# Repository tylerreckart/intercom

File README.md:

# Intercom

A custom, local-first **voice bridge** for [Arbiter](https://arbiter.run): ESP32 (or any client) speaks PCM in, Intercom runs **whisper.cpp** STT + **Kokoro** TTS, and Arbiter stays text + SSE in the middle.

```
ESP32  --WS PCM while PTT held-->  Intercom  --text/SSE-->  arbiter --api
ESP32  <--WS reply PCM-----------  Intercom  <--text------/
```

HTTP `POST /v1/utterance` on `:8090` remains the fallback if the WebSocket is down.

Intercom keeps Whisper and Kokoro loaded in local HTTP servers (`whisper-server` on `:8092`, `scripts/kokoro_server.py` on `:8091`) so each turn does not reload ONNX/ggml. Instant-ack phrases (`Yes, sir.`, `Of course.`, `Very good.`, …) are synthesized once at startup and replayed from PCM cache — including a local ack after `filler.instant_ack_ms` and an earlier tool ack after `filler.tool_ack_ms`. Spoken replies can start after about seven words (`early_flush_words`), not only at a period. Optional WebSocket duplex is `ws://<host>:8093/v1/stream`. Each turn logs a single `intercom latency …` line (`stt_ms`, `arbiter_ttft_ms`, `kokoro_ms`, `ttfa_ms`).

Colocate Intercom on the same host as `arbiter --api` (default `http://127.0.0.1:8080`). Device tokens never see the Arbiter bearer.

The default agent is **Arthur** — a British voice assistant with full Arbiter tool access (`config/arthur.agent.json`). Hallway commands (timers, lights, volume, home weather, next alarm) skip Arbiter when `home.ha_base_url` and `home.ha_token` point at Home Assistant. At boot Intercom sends a silent `PREFIX WARM` turn so a local model can cache Arthur's constitution before the first PTT.

## Build

```bash
cmake -S . -B build -DCMAKE_BUILD_TYPE=Release
cmake --build build -j
```

Requires C++20, CMake 3.20+, SQLite3, Threads. Fetches cpp-httplib and nlohmann/json.

## Configure

```bash
cp config/intercom.example.json intercom.json
# set arbiter_token, paths to whisper-cli + model, kokoro binary + voice
./build/intercom --config intercom.json
```

Install speech tools separately (not vendored):

- [whisper.cpp](https://github.com/ggerganov/whisper.cpp) → `whisper-cli` + `whisper-server` + `ggml-base.en.bin`
- [Kokoro](https://github.com/hexgrad/kokoro) → `kokoro-tts` + ONNX model and voices bundle (Intercom starts `scripts/kokoro_server.py` with that venv)

Set `whisper.use_server` / `kokoro.use_server` to `false` to force the old one-shot CLI path. Point `server_url` at an already-running daemon to skip spawn.

## Quick test (no mic)

Fast-path (skips Arbiter):

```bash
curl -N -H "Authorization: Bearer dev-device-secret-change-me" \
  -H "X-Device-Id: speaker-1" \
  -H "Content-Type: application/json" \
  -d '{"text":"what time is it"}' \
  --output reply.pcm \
  http://127.0.0.1:8090/v1/utterance/text
```

Play: `ffplay -f s16le -ar 16000 -ac 1 reply.pcm`

PCM utterance: see [docs/api.md](docs/api.md) and [docs/device.md](docs/device.md).

## License

Apache-2.0

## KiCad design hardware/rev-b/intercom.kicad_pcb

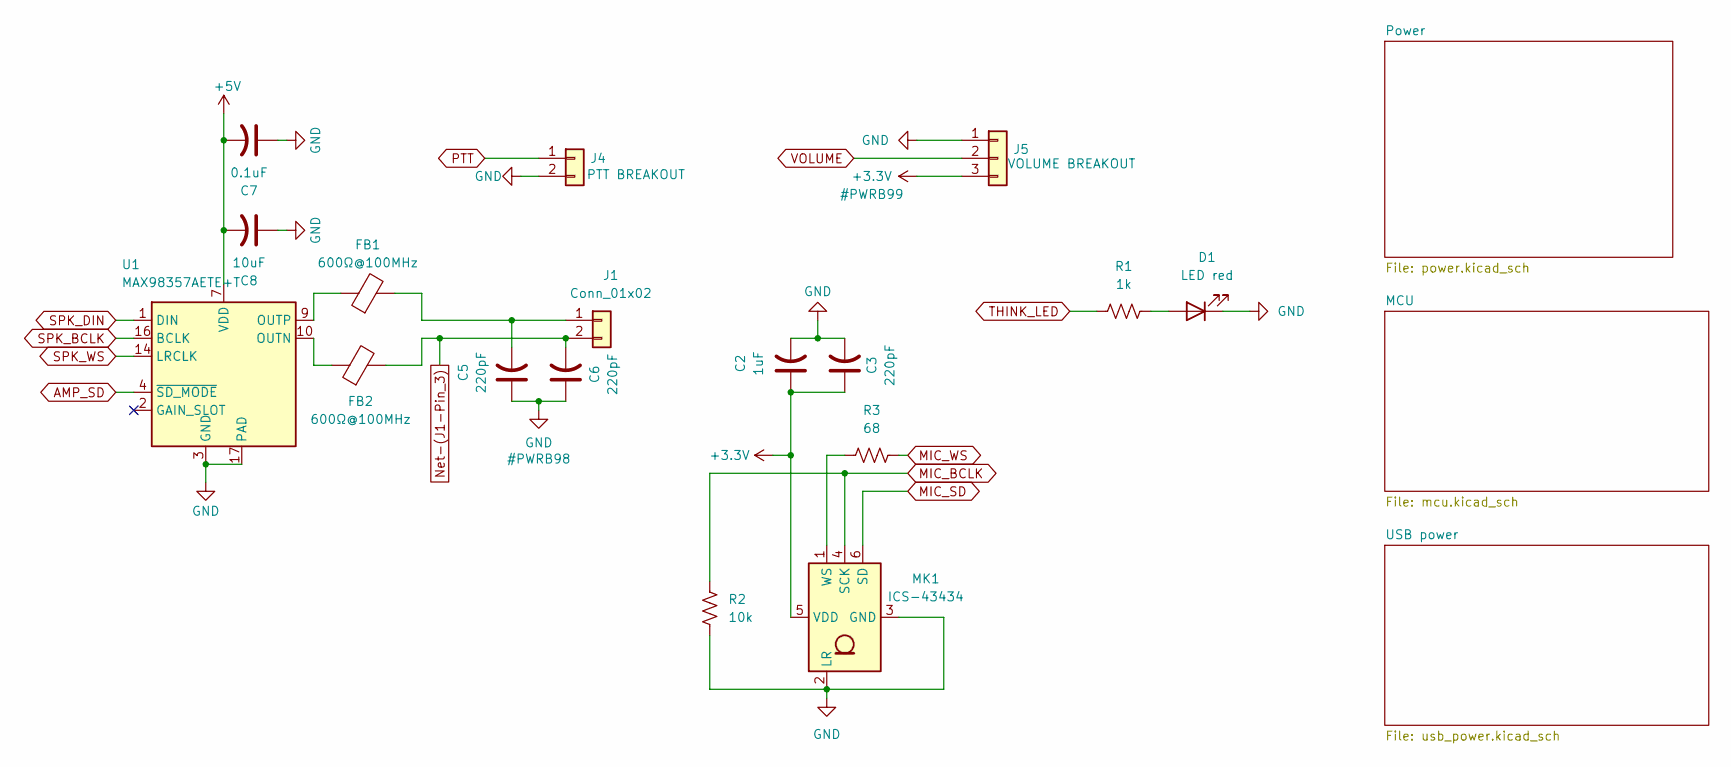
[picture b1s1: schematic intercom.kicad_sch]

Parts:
C2: 1uF; C_0402_1005Metric; MPN CL05A105KO5NNNC; LCSC C29266
C3, C5, C6: 220pF; C_0201_0603Metric; MPN CL03B221KA3NNNC; LCSC C3887425
C7: 0.1uF; C_0201_0603Metric; MPN CL03A104KP3NN5C; LCSC C307382
C8: 10uF; C_0603_1608Metric; MPN CL10A106MO8NQNC; LCSC C92487
D1: LED red; LED_0402_1005Metric; MPN HS-0402-UR; LCSC C1322304
FB1, FB2: 600Ω@100MHz; L_0805_2012Metric_Pad1.05x1.20mm_HandSolder; MPN MPZ2012S601AT000; LCSC C21519
J1: Conn_01x02; JST_PH_S2B-PH-SM4-TB_1x02-1MP_P2.00mm_Horizontal; MPN S2B-PH-SM4-TB(LF)(SN); LCSC C295747
J4: PTT BREAKOUT; JST_PH_S2B-PH-SM4-TB_1x02-1MP_P2.00mm_Horizontal; MPN S2B-PH-SM4-TB(LF)(SN); LCSC C295747
J5: VOLUME BREAKOUT; JST_PH_S3B-PH-SM4-TB_1x03-1MP_P2.00mm_Horizontal; MPN S3B-PH-SM4-TB; LCSC C20089272
MK1: ICS-43434; InvenSense_ICS-43434-6_3.5x2.65mm; MPN ICS-43434; LCSC C5656610
R1: 1k; R_0201_0603Metric; MPN 0201WMF1001TEE; LCSC C270365
R2: 10k; R_0201_0603Metric; MPN 0201WMF1002TEE; LCSC C473048
R3: 68; R_0201_0603Metric; MPN 0201WMF680JTEE; LCSC C473537
U1: MAX98357AETE+T; TQFN-16-1EP_3x3mm_P0.5mm_EP1.23x1.23mm_ThermalVias; MPN MAX98357AETE+T; LCSC C910544

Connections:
+3.3V: C2.1, C3.1, J5.3, MK1.5 (VDD); also elsewhere on the board
+5V: C7.2, C8.2, U1.7 (VDD), U1.8 (VDD); also elsewhere on the board
AMP_SD: U1.4 (~SD_MODE); also elsewhere on the board
GND: C2.2, C3.2, C5.1, C6.1, C7.1, C8.1, D1.1 (K), J4.2, J5.1, MK1.2 (LR), MK1.3 (GND), R2.1, U1.3 (GND), U1.11 (GND), U1.15 (GND), U1.17 (PAD); also elsewhere on the board
MIC_BCLK: MK1.4 (SCK), R2.2; also elsewhere on the board
MIC_SD: MK1.6 (SD); also elsewhere on the board
MIC_WS: R3.1; also elsewhere on the board
unnamed: D1.2 (A), R1.2
unnamed: C5.2, FB1.2, J1.1
unnamed: C6.2, FB2.2, J1.2
unnamed: MK1.1 (WS), R3.2
unnamed: FB2.1, U1.10 (OUTN)
unnamed: FB1.1, U1.9 (OUTP)
PTT: J4.1; also elsewhere on the board
SPK_BCLK: U1.16 (BCLK); also elsewhere on the board
SPK_DIN: U1.1 (DIN); also elsewhere on the board
SPK_WS: U1.14 (LRCLK); also elsewhere on the board
THINK_LED: R1.1; also elsewhere on the board
VOLUME: J5.2; also elsewhere on the board

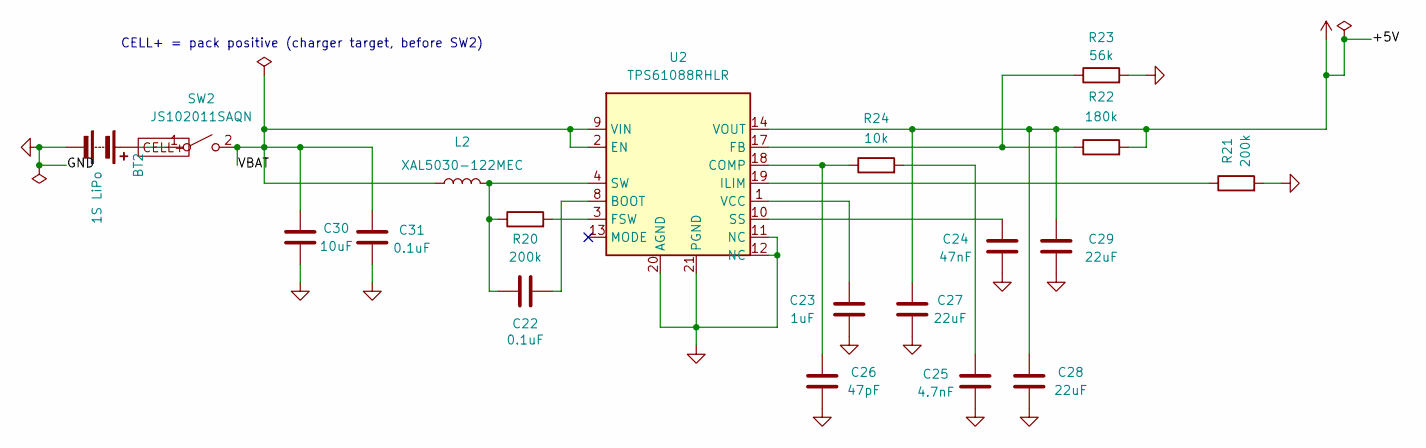
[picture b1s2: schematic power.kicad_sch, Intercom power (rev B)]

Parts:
BT2: 1S LiPo; JST_PH_S2B-PH-SM4-TB_1x02-1MP_P2.00mm_Horizontal; MPN S2B-PH-SM4-TB(LF)(SN); LCSC C295747
C22, C31: 0.1uF; C_0201_0603Metric; MPN CL03A104KP3NN5C; LCSC C307382
C23: 1uF; C_0402_1005Metric; MPN CL05A105KO5NNNC; LCSC C29266
C24: 47nF; C_0201_0603Metric; MPN 0201X473K100NT; LCSC C880416
C25: 4.7nF; C_0201_0603Metric; MPN 0201B472K100NT; LCSC C285054
C26: 47pF; C_0201_0603Metric; MPN 0201CG470J500NT; LCSC C62546
C27, C28, C29: 22uF; C_0805_2012Metric; MPN CL21A226MAQNNNE; LCSC C45783
C30: 10uF; C_0603_1608Metric; MPN CL10A106MO8NQNC; LCSC C92487
L2: XAL5030-122MEC; L_Coilcraft_XAL5030-XXX; MPN XAL5030-122MEC; LCSC C7471471
R20, R21: 200k; R_0201_0603Metric; MPN 0201WMF2003TCE; LCSC C62188
R22: 180k; R_0201_0603Metric; MPN 0201WMF1803TEE; LCSC C473559
R23: 56k; R_0201_0603Metric; MPN 0201WMF5602TEE; LCSC C473524
R24: 10k; R_0201_0603Metric; MPN 0201WMF1002TEE; LCSC C473048
SW2: JS102011SAQN; SW_SPDT_CK_JS102011SAQN; MPN JS102011SAQN; LCSC C221660
U2: TPS61088RHLR; Texas_VQFN-RHL-20_ThermalVias; MPN TPS61088RHLR; LCSC C87357

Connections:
+5V: C27.1, C28.1, C29.1, R22.2, U2.14 (VOUT), U2.15 (VOUT), U2.16 (VOUT); also elsewhere on the board
/Power/VBAT: C30.1, C31.1, L2.1, SW2.2 (B), U2.2 (EN), U2.9 (VIN)
CELL+: BT2.1 (+), SW2.1 (A); also elsewhere on the board
GND: BT2.2 (-), C23.2, C24.2, C25.2, C26.2, C27.2, C28.2, C29.2, C30.2, C31.2, R21.2, R23.2, U2.11 (NC), U2.12 (NC), U2.20 (AGND), U2.21 (PGND); also elsewhere on the board
unnamed: C22.2, L2.2, R20.1, U2.4 (SW), U2.5 (SW), U2.6 (SW), U2.7 (SW)
unnamed: C25.1, R24.2
unnamed: C22.1, U2.8 (BOOT)
unnamed: C26.1, R24.1, U2.18 (COMP)
unnamed: R22.1, R23.1, U2.17 (FB)
unnamed: R20.2, U2.3 (FSW)
unnamed: R21.1, U2.19 (ILIM)
unnamed: C24.1, U2.10 (SS)
unnamed: C23.1, U2.1 (VCC)

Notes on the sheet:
CELL+ = pack positive (charger target, before SW2)

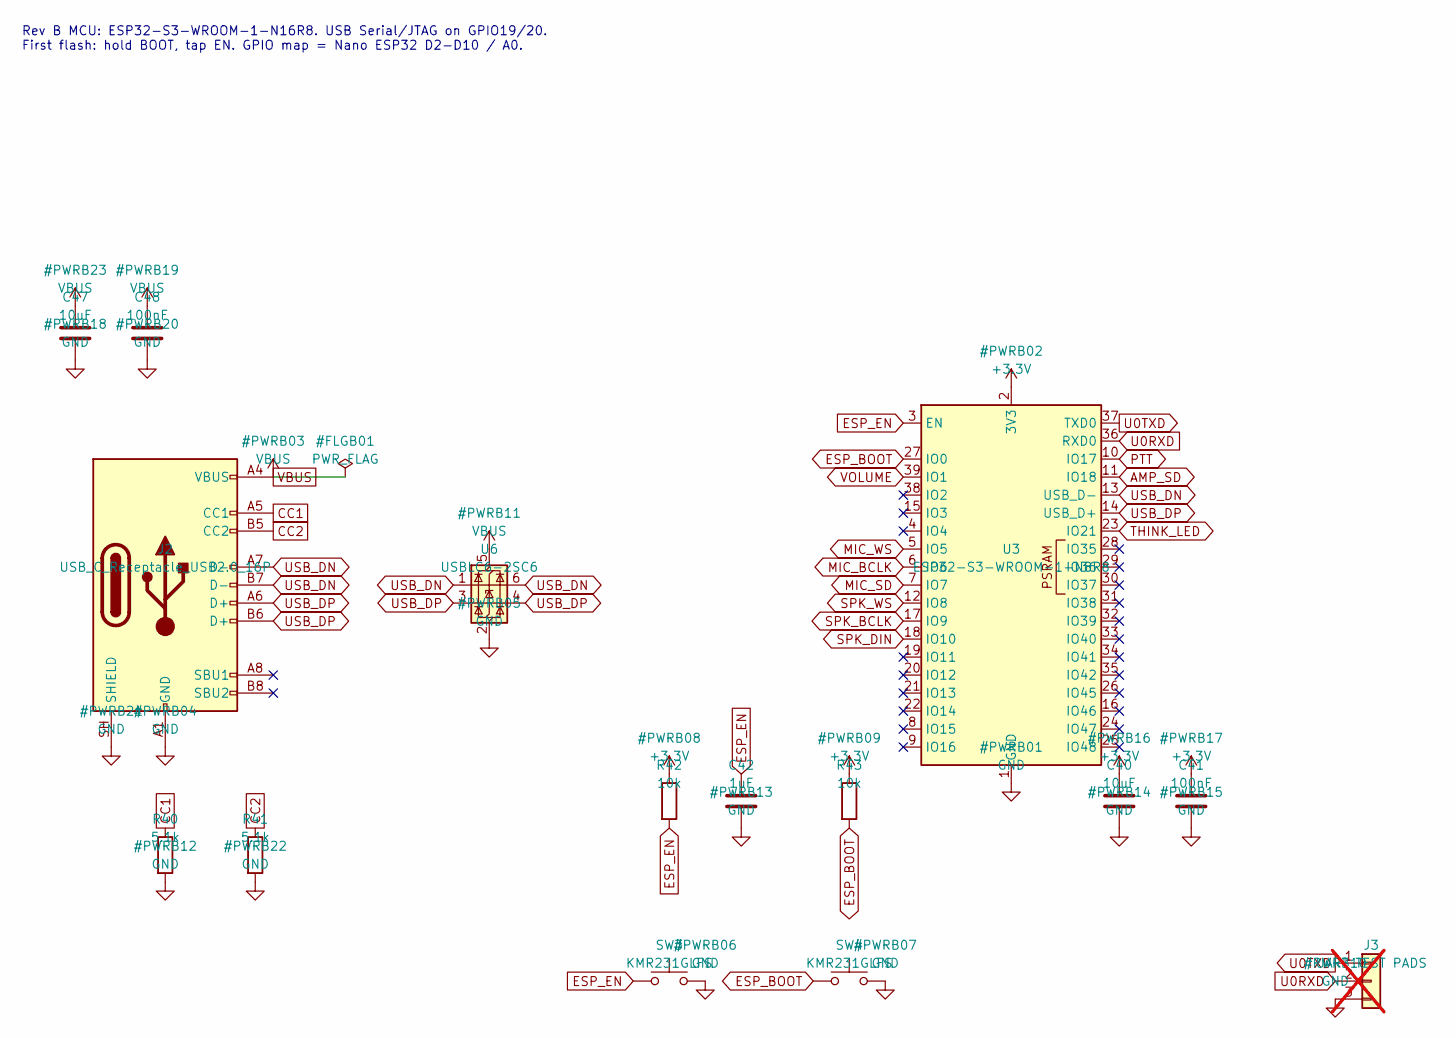
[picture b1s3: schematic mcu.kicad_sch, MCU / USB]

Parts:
C40, C47: 10uF; C_0603_1608Metric; MPN CL10A106MO8NQNC; LCSC C92487
C41, C48: 100nF; C_0201_0603Metric; MPN CL03A104KP3NN5C; LCSC C307382
C42: 1uF; C_0402_1005Metric; MPN CL05A105KO5NNNC; LCSC C29266
J2: USB_C_Receptacle_USB2.0_16P; USB_C_Receptacle_HRO_TYPE-C-31-M-12; MPN TYPE-C-31-M-12; LCSC C165948
J3: UART TEST PADS; UART_TestPads_3Pin; not fitted
R40, R41: 5.1k; R_0201_0603Metric; MPN 0201WMF5101TEE; LCSC C270344
R42, R43: 10k; R_0201_0603Metric; MPN 0201WMF1002TEE; LCSC C473048
SW3, SW4: KMR231GLFS; SW_Push_1P1T_NO_CK_KMR2; MPN KMR231GLFS; LCSC C99271
U3: ESP32-S3-WROOM-1-N8R8; ESP32-S3-WROOM-1; MPN ESP32-S3-WROOM-1-N8R8; LCSC C2913201
U6: USBLC6-2SC6; SOT-23-6; MPN USBLC6-2SC6; LCSC C7519

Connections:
+3.3V: C40.1, C41.1, R42.1, R43.1, U3.2 (3V3); also elsewhere on the board
AMP_SD: U3.11 (IO18); also elsewhere on the board
CC1: J2.A5 (CC1), R40.1
CC2: J2.B5 (CC2), R41.1
ESP_BOOT: R43.2, SW4.1, U3.27 (IO0)
ESP_EN: C42.1, R42.2, SW3.1, U3.3 (EN)
GND: C40.2, C41.2, C42.2, C47.2, C48.2, J2.A1 (GND), J2.A12 (GND), J2.B1 (GND), J2.B12 (GND), J2.SH (SHIELD), J3.3, R40.2, R41.2, SW3.2, SW4.2, U3.1 (GND), U3.40 (GND), U3.41 (GND), U6.2 (GND); also elsewhere on the board
MIC_BCLK: U3.6 (IO6); also elsewhere on the board
MIC_SD: U3.7 (IO7); also elsewhere on the board
MIC_WS: U3.5 (IO5); also elsewhere on the board
PTT: U3.10 (IO17); also elsewhere on the board
SPK_BCLK: U3.17 (IO9); also elsewhere on the board
SPK_DIN: U3.18 (IO10); also elsewhere on the board
SPK_WS: U3.12 (IO8); also elsewhere on the board
THINK_LED: U3.23 (IO21); also elsewhere on the board
U0RXD: J3.2, U3.36 (RXD0)
U0TXD: J3.1, U3.37 (TXD0)
USB_DN: J2.A7 (D-), J2.B7 (D-), U3.13 (USB_D-), U6.1 (I/O1), U6.6 (I/O1)
USB_DP: J2.A6 (D+), J2.B6 (D+), U3.14 (USB_D+), U6.3 (I/O2), U6.4 (I/O2)
VBUS: C47.1, C48.1, J2.A4 (VBUS), J2.A9 (VBUS), J2.B4 (VBUS), J2.B9 (VBUS), U6.5 (VBUS); also elsewhere on the board
VOLUME: U3.39 (IO1); also elsewhere on the board

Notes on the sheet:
Rev B MCU: ESP32-S3-WROOM-1-N16R8. USB Serial/JTAG on GPIO19/20. First flash: hold BOOT, tap EN. GPIO map = Nano ESP32 D2-D10 / A0.

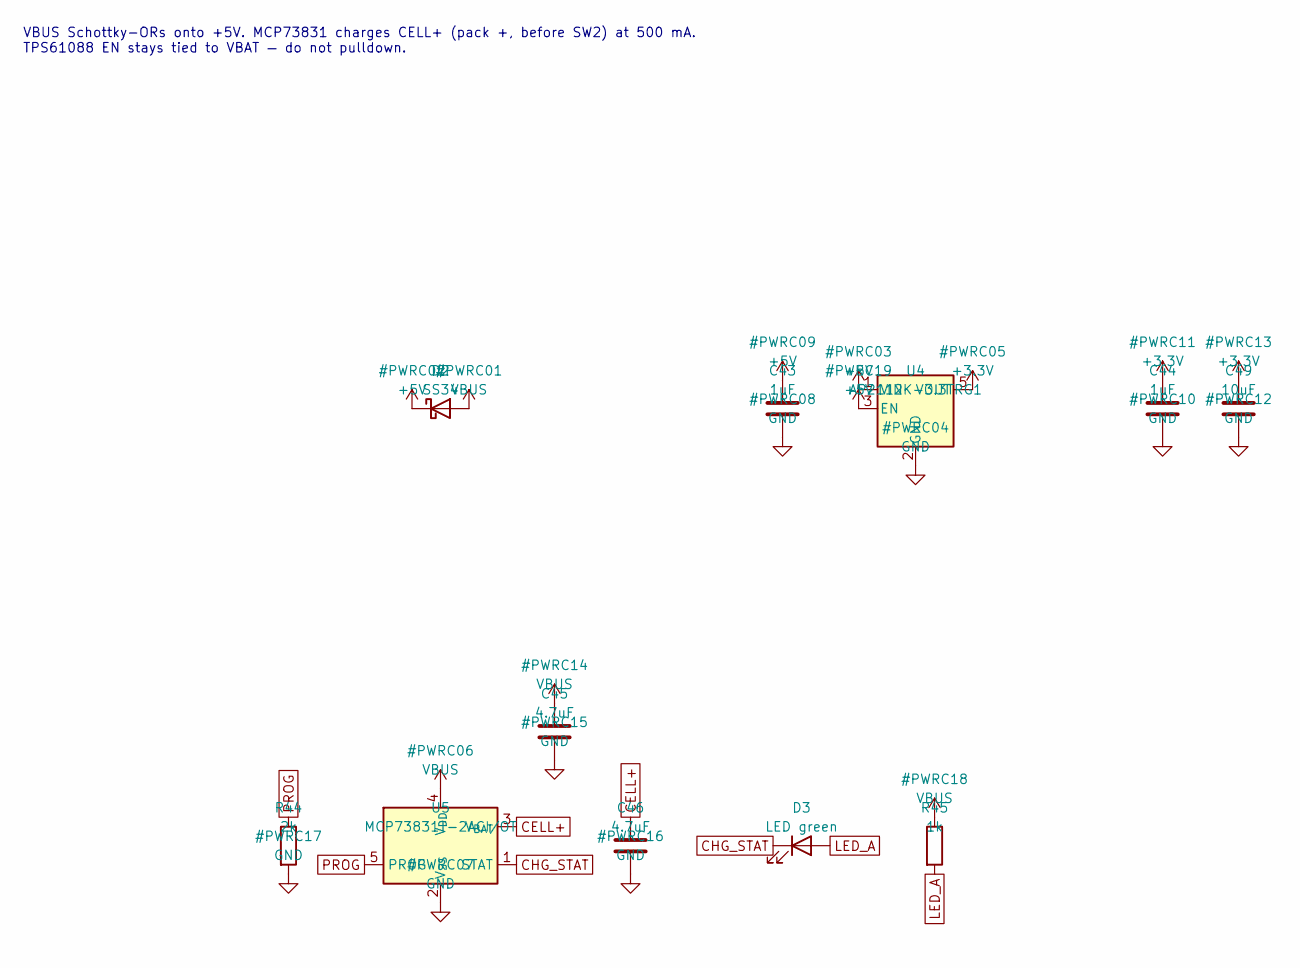
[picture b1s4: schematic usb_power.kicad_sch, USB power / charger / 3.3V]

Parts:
C43, C44: 1uF; C_0402_1005Metric; MPN CL05A105KO5NNNC; LCSC C29266
C45, C46: 4.7uF; C_0402_1005Metric; MPN CL05A475MP5NRNC; LCSC C23733
C49: 10uF; C_0603_1608Metric; MPN CL10A106MO8NQNC; LCSC C92487
D2: SS34; D_SMA; MPN SS34; LCSC C727060
D3: LED green; LED_0402_1005Metric; MPN HS-0402-UG; LCSC C1322308
R44: 2k; R_0201_0603Metric; MPN 0201WMF2001TEE; LCSC C270358
R45: 1k; R_0201_0603Metric; MPN 0201WMF1001TEE; LCSC C270365
U4: AP2112K-3.3TRG1; SOT-23-5; MPN AP2112K-3.3TRG1; LCSC C51118
U5: MCP73831T-2ACI/OT; SOT-23-5; MPN MCP73831T-2ACI/OT; LCSC C424093

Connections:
+3.3V: C44.1, C49.1, U4.5 (VOUT); also elsewhere on the board
+5V: C43.1, D2.1 (K), U4.1 (VIN), U4.3 (EN); also elsewhere on the board
CELL+: C46.1, U5.3 (V_{BAT}); also elsewhere on the board
CHG_STAT: D3.1 (K), U5.1 (STAT)
GND: C43.2, C44.2, C45.2, C46.2, C49.2, R44.2, U4.2 (GND), U5.2 (V_{SS}); also elsewhere on the board
LED_A: D3.2 (A), R45.2
PROG: R44.1, U5.5 (PROG)
VBUS: C45.1, D2.2 (A), R45.1, U5.4 (V_{DD}); also elsewhere on the board

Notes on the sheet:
VBUS Schottky-ORs onto +5V. MCP73831 charges CELL+ (pack +, before SW2) at 500 mA. TPS61088 EN stays tied to VBAT — do not pulldown.

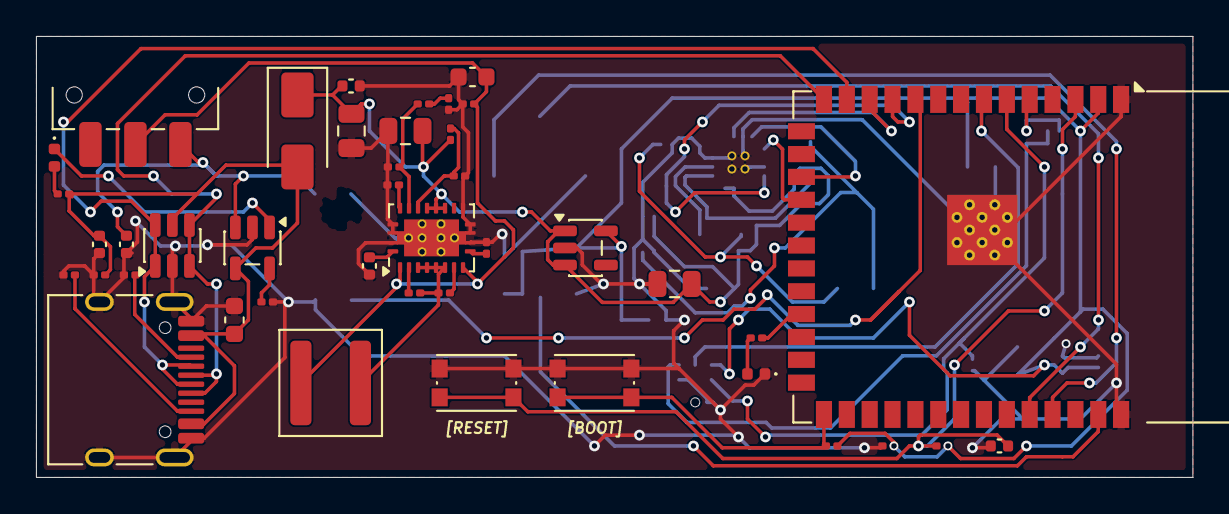
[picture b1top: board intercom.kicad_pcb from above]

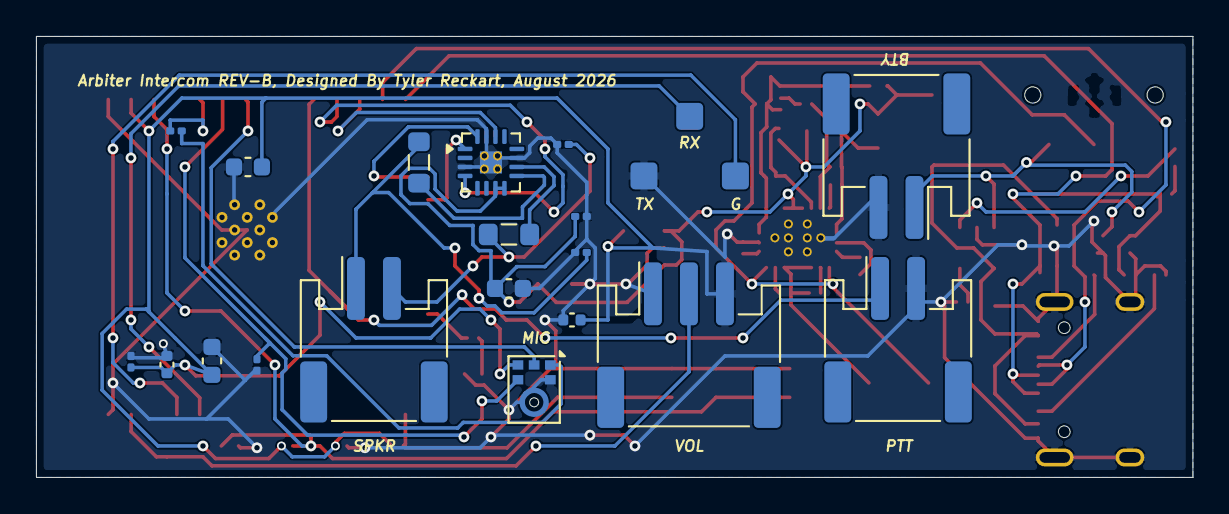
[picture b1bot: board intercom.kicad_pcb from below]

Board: 2 copper layers, 64.2 x 24.5 mm, 62 parts (20 on the bottom side), 42 nets.

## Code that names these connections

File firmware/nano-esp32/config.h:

#pragma once

// Copy this file's WIFI_* / INTERCOM_TOKEN values, or create secrets.h next to
// the sketch (gitignored) with #define WIFI_SSID, WIFI_PASSWORD, INTERCOM_TOKEN.

#if __has_include("secrets.h")
#include "secrets.h"
#endif

#ifndef WIFI_SSID
#define WIFI_SSID "YOUR_WIFI_SSID"
#endif
#ifndef WIFI_PASSWORD
#define WIFI_PASSWORD "YOUR_WIFI_PASSWORD"
#endif

#ifndef INTERCOM_HOST
// LAN IP of the machine running Intercom — not 127.0.0.1 (that is the ESP itself).
#define INTERCOM_HOST "192.168.86.40"
#endif
#define FIRMWARE_CONFIG_TAG "intercom-lan-v1"
#ifndef INTERCOM_PORT
#define INTERCOM_PORT 8090
#endif
#ifndef INTERCOM_TOKEN
#define INTERCOM_TOKEN "dev-device-secret-change-me"
#endif
#ifndef INTERCOM_DEVICE_ID
#define INTERCOM_DEVICE_ID ""
#endif

#define SAMPLE_RATE 24000
#define MAX_RECORD_MS 8000
#define MIN_RECORD_MS 400
#define HEADER_TIMEOUT_MS 120000
#define HTTP_TIMEOUT_MS 15000
#define AUDIO_WAIT_MS HEADER_TIMEOUT_MS

// Silkscreen D# / A0 labels — correct in either IDE pin numbering mode.
#define PIN_MIC_WS D2
#define PIN_MIC_BCLK D3
#define PIN_MIC_SD D4
#define PIN_SPK_WS D5
#define PIN_SPK_BCLK D6
#define PIN_SPK_DIN D7
#define PIN_PTT D8       // to GND, INPUT_PULLUP
#define PIN_AMP_SD D9    // MAX98357A SD (HIGH=on, LOW=mute)
#define PIN_THINK_LED D10
#define THINK_BLINK_MS 250
#define PIN_VOLUME A0    // A50k wiper (ends to 3V3 and GND)
#define ADC_MAX 4095
#define VOL_UPDATE_MS 30

// Mic family — set before flashing when you swap breakouts.
#define MIC_ICS43434 0  // INMP441 and clones use the same I2S timing
#define MIC_SPH0645 1   // Adafruit SPH0645LM4H (ICS-43434 drop-in wiring)
#ifndef MIC_TYPE
#define MIC_TYPE MIC_ICS43434
#endif

// SEL/L/R tied to GND => left slot. Set 0 if SEL is tied to 3V3.
#define MIC_LEFT_SLOT 1

// Log mic pin map + OUT activity on every PTT capture.
#ifndef MIC_PTT_PIN_DEBUG
#define MIC_PTT_PIN_DEBUG 1
#endif
